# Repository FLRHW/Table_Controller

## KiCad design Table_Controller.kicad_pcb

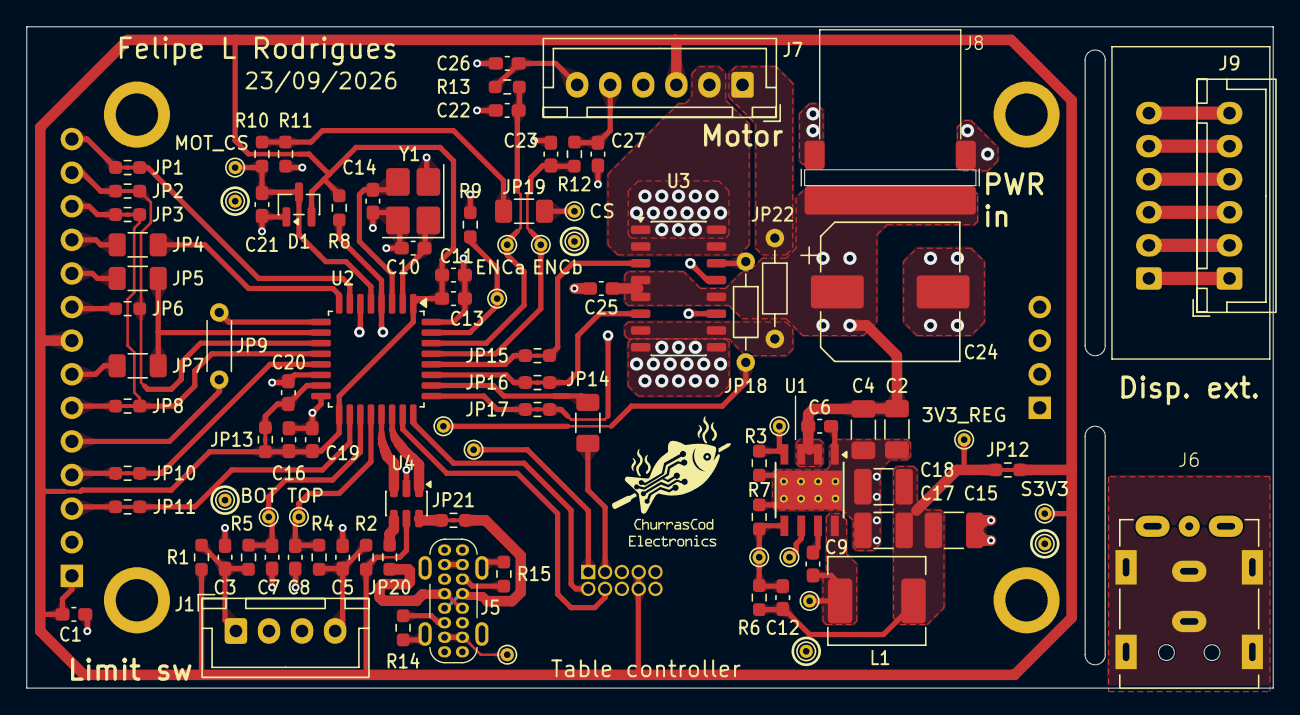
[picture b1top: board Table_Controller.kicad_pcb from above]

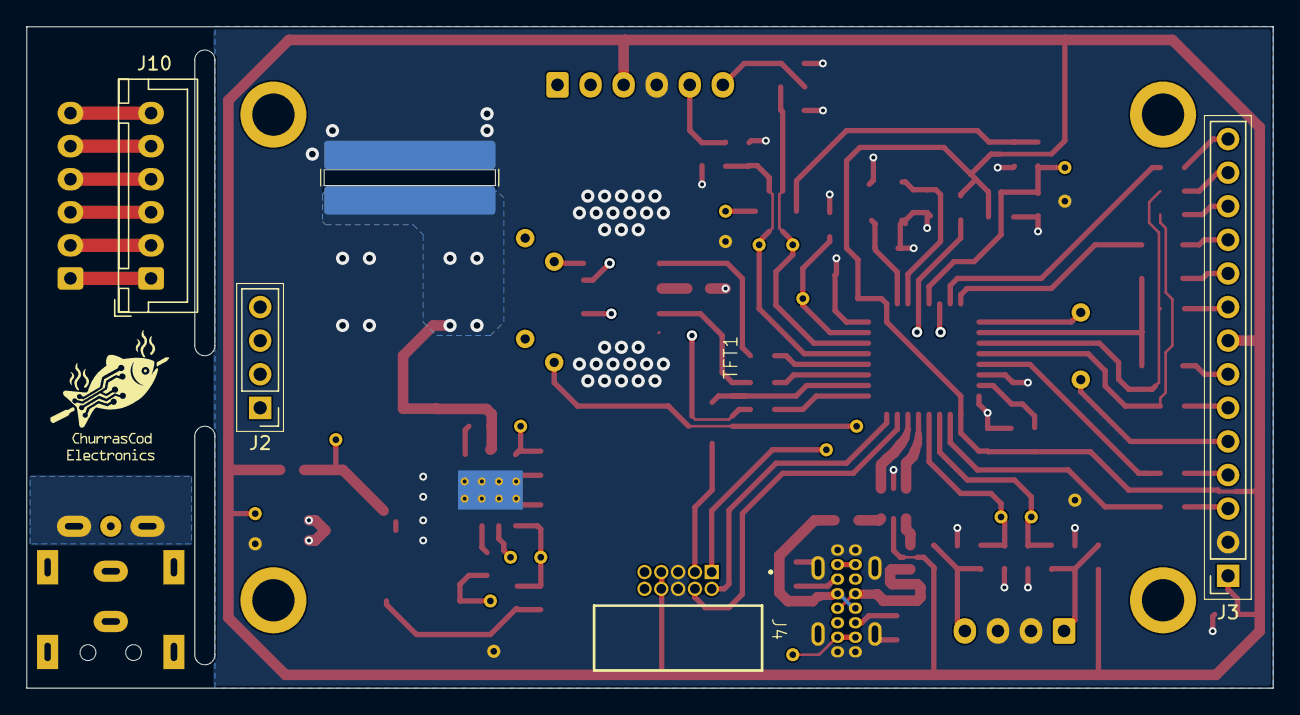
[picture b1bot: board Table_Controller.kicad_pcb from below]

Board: 4 copper layers, 94.2 x 50.0 mm, 103 parts (5 on the bottom side), 75 nets.

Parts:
C1, C6, C9, C13, C19, C20, C25: 100n; C_0603_1608Metric_Pad1.08x0.95mm_HandSolder
C2, C4: 4.7u; C_1206_3216Metric_Pad1.33x1.80mm_HandSolder
C3, C5, C26, C27: 10n; C_0603_1608Metric_Pad1.08x0.95mm_HandSolder
C7, C8, C21, C22, C23: 1n; C_0603_1608Metric_Pad1.08x0.95mm_HandSolder
C10, C14: 22p; C_0603_1608Metric_Pad1.08x0.95mm_HandSolder
C11, C16: 1u; C_0603_1608Metric_Pad1.08x0.95mm_HandSolder
C12: 33p; C_0603_1608Metric_Pad1.08x0.95mm_HandSolder
C15, C17, C18: 22u; C_1210_3225Metric_Pad1.33x2.70mm_HandSolder
C24: 220u; CP_Elec_10x10
D1: BAV99; SOT-23
J1: JST B4B XH A; JST_XH_B4B-XH-A_1x04_P2.50mm_Vertical
J2: 2.54 mm header; PinHeader_1x04_P2.54mm_Vertical
J3: Conn_01x14_Pin; PinSocket_1x14_P2.54mm_Vertical
J4: HX JN1.27-2x5 WZ H4.9; JN1.27-2x5 WZ H4.9
J5: USB_C_Receptacle_USB2.0_16P; USB_C_socket_16P_vertical
J6: Dell DC jack
J7, J9, J10: JST B6B XH A; JST_XH_B6B-XH-A_1x06_P2.50mm_Vertical
J8: DC barrel assy; Dell_barrel_assy
JP1, JP2, JP3, JP8, JP10, JP11, JP12, JP13, JP15, JP16, JP17, JP21: 0R; Jumper_0603
JP4, JP5, JP7, JP14, JP19: 0R; R_1206_3216Metric_Pad1.30x1.75mm_HandSolder
JP6, JP20: 0R; R_0603_1608Metric_Pad0.98x0.95mm_HandSolder
JP9: 0R; R_Axial_DIN0204_L3.6mm_D1.6mm_P5.08mm_Horizontal
JP18, JP22: 0R; R_Axial_DIN0204_L3.6mm_D1.6mm_P7.62mm_Horizontal
L1: 10u; L_Bourns_SRP6540
R1, R2, R7, R8, R9: 10k; R_0603_1608Metric_Pad0.98x0.95mm_HandSolder
R3: 64.9k; R_0603_1608Metric_Pad0.98x0.95mm_HandSolder
R4, R5, R10, R12, R13: 2k2; R_0603_1608Metric_Pad0.98x0.95mm_HandSolder
R6: 23.2k; R_0603_1608Metric_Pad0.98x0.95mm_HandSolder
R11: 820; R_0603_1608Metric_Pad0.98x0.95mm_HandSolder
R14, R15: 5k1; R_0603_1608Metric_Pad0.98x0.95mm_HandSolder
TFT1: TFT_2.4in_320x240; Display_240x320_ILI9341_2.4in_no_pads
TP1, TP2, TP3, TP4, TP5, TP6, TP7, TP8, TP9, TP10, TP11, TP12, TP13, TP14, TP15, TP16, TP17, TP18, TP19, TP20, TP21: TestPoint; TestPoint_THTPad_D1.0mm_Drill0.5mm
U1: LMR380x0; Texas_HSOP-8-1EP_3.9x4.9mm_P1.27mm_ThermalVias
U2: STM32G431K8Tx; LQFP-32_7x7mm_P0.8mm
U3: VNH7070; JEITA_SOIC-16_3.9x9.9mm_P1.27mm
U4: USBLC6-2SC6; SOT-23-6
Y1: 20 MHz; Crystal_SMD_3225-4Pin_3.2x2.5mm_HandSoldering

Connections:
/3V3_REG: C12.1, C15.1, C17.1, C18.1, JP12.1, L1.2, R6.1, TP7.1 (1_1)
/BOOT0: R9.1, TP9.1 (1_1), U2.31 (PB8)
/BOT_EOT: C3.1, J1.1, R1.2, R5.1
/BOT_filt: C7.1, R5.2, TP4.1 (1_1), U2.19 (PA9)
/CC1: J5.A5 (CC1), R14.1
/CC2: J5.B5 (CC2), R15.1
/CS': JP19.2, TP15.1 (1_1), U3.13 (CS)
/D+: J5.A6 (D+), J5.B6 (D+), JP21.1
/D+': JP21.2, U4.6 (I/O1)
/D-: J5.A7 (D-), J5.B7 (D-), JP20.1
/D-': JP20.2, U4.4 (I/O2)
/DISP_CS: JP11.1, U2.18 (PA8)
/DISP_DC: JP9.1, U2.9 (PA4)
/DISP_MISO: JP2.1, JP6.1, U2.11 (PA6)
/DISP_MOSI: JP3.1, JP8.1, U2.12 (PA7)
/DISP_RST: JP10.1, U2.13 (PB0)
/DISP_SCK: JP5.1, JP7.1, U2.10 (PA5)
/ENCa: C27.1, J7.5, R12.2
/ENCa_filt: C23.1, R12.1, TP12.1 (1_1), U2.29 (PB6)
/ENCb: C26.1, J7.6, R13.2
/ENCb_filt: C22.1, R13.1, TP13.1 (1_1), U2.30 (PB7)
/FB: C12.2, R6.2, R7.1, TP5.1 (1_1), U1.5 (FB)
/GND: C1.2, C2.2, C3.2, C4.2, C5.2, C6.2, C7.2, C8.2, C10.2, C11.2, C13.2, C14.2, C15.2, C16.2, C17.2, C18.2, C19.2, C20.2, C21.2, C22.2, C23.2, C24.2, C25.2, C26.2, C27.2, D1.1 (K), J1.2, J1.3, J3.2, J4.5, J4.6, J5.A1 (GND), J5.A12 (GND), J5.B1 (GND), J5.B12 (GND), J5.SH (SHIELD), J7.4, J8.2 (-), R3.2, R7.2, R9.2, R11.2, R14.2, R15.2, TP17.1 (1_1), TP18.1 (1_1), TP19.1 (1_1), TP20.1 (1_1), TP21.1 (1_1), U1.1 (GND), U1.9 (EP), U2.14 (VSSA), U2.16 (VSS), U2.32 (VSS), U3.1 (GNDa), U3.8 (GNDb), U3.9 (GNDb), U3.16 (GNDa), U4.2 (GND), Y1.2 (G), Y1.4 (G)
/GND_2: J6.3 (-), J6.SH
/INa: JP15.1, U2.28 (PB5)
/INa': JP15.2, U3.3 (INa)
/INb: JP16.1, U2.27 (PB4)
/INb': JP16.2, U3.6 (INb)
/MOT_CS: C21.1, D1.3 (K), R10.1, TP14.1 (1_1), U2.5 (PA0)
/NRST: J4.1, R8.2, TP8.1 (1_1), U2.4 (PG10)
/OUTa: J7.2, U3.2 (OUTa), U3.15 (OUTa)
/OUTb: J7.1, JP22.1
/OUTb': JP22.2, U3.7 (OUTb), U3.10 (OUTb)
/PG: TP1.1 (1_1), U1.6 (PG)
/PWM: JP17.1, U2.25 (PA15)
/PWM': JP17.2, U3.11 (PWM)
/RT: R3.1, TP2.1 (1_1), U1.4 (RT/SYNC)
/S3V3: C1.1, C11.1, C13.1, C16.1, C19.1, D1.2 (A), J3.1, J3.8, J4.7, J4.8, J7.3, JP12.2, JP13.1, R1.1, R2.1, R8.1, TP10.1 (1_1), U2.1 (VDD), U2.17 (VDD), U4.5 (VBUS)
/S3V3_A: C20.1, JP13.2, U2.15 (VDDA)
/S19V5: C2.1, C4.1, C6.1, C24.1, C25.1, J8.1 (+), U1.2 (EN), U1.3 (VIN), U3.4 (VCC), U3.5 (VCC), U3.12 (VCC)
/SEL0: JP18.2, TP11.1 (1_1), U2.6 (PA1)
/SEL0': JP18.1, U3.14 (SEL0)
/SW: C9.2, L1.1, TP6.1 (1_1), U1.8 (SW)
/SWDCLK: J4.2, U2.24 (PA14)
/SWDIO: J4.4, U2.23 (PA13)
/SWO: JP14.1, U2.26 (PB3)
/SWO': J4.3, JP14.2
/TCH_CS: JP4.1, U2.8 (PA3)
/TCH_IRQ: JP1.1, U2.7 (PA2)
/TOP_EOT: C5.1, J1.4, R2.2, R4.1
/TOP_filt: C8.1, R4.2, TP3.1 (1_1), U2.20 (PA10)
/USB_DM: U2.21 (PA11), U4.3 (I/O2)
/USB_DP: U2.22 (PA12), U4.1 (I/O1)
/XIN: C10.1, U2.2 (PF0), Y1.1
/XOUT: C14.1, U2.3 (PF1), Y1.3
unnamed: J3.3, JP11.2
unnamed: J3.4, JP10.2
unnamed: J3.5, JP9.2
unnamed: J3.6, JP8.2
unnamed: J3.7, JP7.2
unnamed: J3.9, JP6.2
unnamed: J3.10, JP5.2
unnamed: J3.11, JP4.2
unnamed: J3.12, JP3.2
unnamed: J3.13, JP2.2
unnamed: J3.14, JP1.2
unnamed: J5.A4 (VBUS), J5.A9 (VBUS), J5.B4 (VBUS), J5.B9 (VBUS), TP16.1 (1_1)
unnamed: J9.1, J10.1
unnamed: J9.2, J10.2
unnamed: J9.3, J10.3
unnamed: J9.4, J10.4
unnamed: J9.5, J10.5
unnamed: J9.6, J10.6
unnamed: JP19.1, R10.2, R11.1
unnamed: C9.1, U1.7 (BOOT)
